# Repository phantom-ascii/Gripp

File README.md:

# Gripp
A beutifully simple robot arm (ive never done robotics)

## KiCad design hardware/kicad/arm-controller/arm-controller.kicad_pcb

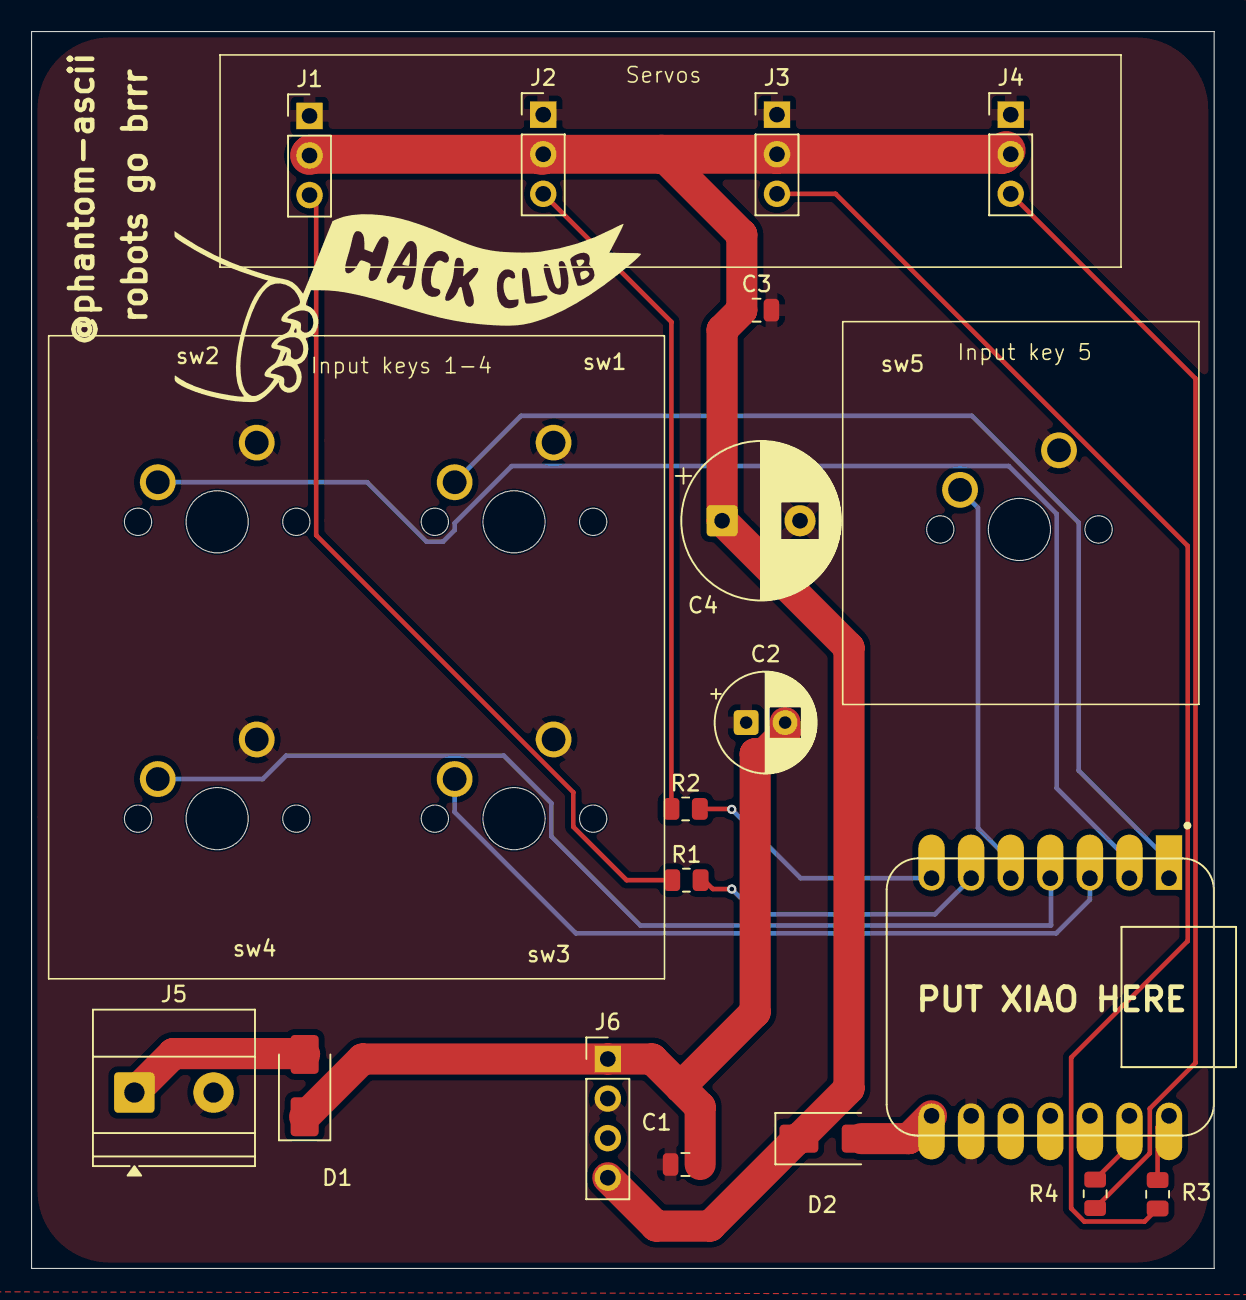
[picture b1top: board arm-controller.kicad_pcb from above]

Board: 2 copper layers, 75.9 x 79.4 mm, 23 parts (1 on the bottom side), 18 nets.

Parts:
 : LOGO
C1, C3: 100nF; C_0805_2012Metric
C2: 220uF; CP_Radial_D6.3mm_P2.50mm
C4: 1000uF; CP_Radial_D10.0mm_P5.00mm
D1: SS34; D_SMA
D2: SS14; D_SMA
J1, J2, J3, J4: Conn_01x03_Pin; PinHeader_1x03_P2.54mm_Vertical
J5: Screw_Terminal_01x02; TerminalBlock_Phoenix_MKDS-1,5-2-5.08_1x02_P5.08mm_Horizont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
J6: Conn_01x04_Pin; PinHeader_1x04_P2.54mm_Vertical
MX1: sw1; SW_MX_1u
MX2: sw2; SW_MX_1u
MX3: sw3; SW_MX_1u
MX4: sw4; SW_MX_1u
MX5: sw5; SW_MX_1u
R1, R2, R3, R4: 220Ω; R_0805_2012Metric
U1: Seeeduino Xiao rp2040; XIAO-Generic-Hybrid-14P-2.54-21X17.8MM

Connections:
+5V_SERVO: C3.1, C4.1, D2.1 (K), J1.2, J2.2, J3.2, J4.2, J6.4
GND: C1.1, C2.1, C3.2, C4.2, J1.1, J2.1, J3.1, J4.1, J5.2, J6.2, MX1.2, MX2.2, MX3.2, MX4.2, MX5.2, U1.9 (GND)
GP1: MX1.1, U1.1 (P26)
GP2: MX2.1, U1.2 (P27)
GP3: MX3.1, U1.3 (P28)
GP4: MX4.1, U1.4 (P29)
GP5: MX5.1, U1.5 (P6)
unnamed: D2.2 (A), U1.8 (5V)
unnamed: J1.3, R1.1
unnamed: J2.3, R2.1
unnamed: J3.3, R3.1
unnamed: J4.3, R4.1
SERVO1: R1.2, U1.6 (P7)
SERVO2: R2.2, U1.7 (P0)
SERVO3: R3.2, U1.14 (P1)
SERVO4: R4.2, U1.13 (P2)
VIN: D1.2 (A), J5.1
V_UNREG: C1.2, C2.2, D1.1 (K), J6.1
